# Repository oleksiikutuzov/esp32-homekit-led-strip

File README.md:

# esp32-homekit-led-strip
Native Apple HomeKit via an ESP32 for the NeoPixel LED Strip or any 5V LED Strip

Software is based on [HomeSpan](https://github.com/HomeSpan/HomeSpan) library. Supports RGB or RGBW Neopixel strips and optionally can act like a switch for any 5V electronics (Switch accessory in HomeKit can be shown as a Bulb, Socket or Fan).

_As usual, don't expect any warranties. I am just a hobbyist, not a professional. It works for me, but you take your own risk using it. I am not liable for any damage to your devices._

## Hardware

Custom PCB is designed for the project. Currently for regular ESP32 board, however there are plans to do for ESP32-C3, which has smaller footprint.

## HomeKit functions

Device has three modes, which can be switched via the Eve app. As they are custim characteristics, they are not visible in the Home app:
* Manual Control (manually set one single color)
* Rainbow (the whole strip is changing colors)
* Color Wheel (strip has different colors "running" along)

Also in the Eve app you can set the number of LEDs in your strip (default is 90). After changing this characteristic, you need to restart the controller for changes to take effect. 

Characteristics values are saved to NVS, so they will be restored if device looses power. 

At the moment you can enable the Switch device in the sketch by defining the `RELAY` variable, but in the future this will implemented via custom characteristic as well to be able to enable it when device is running.

## Software

Here you can see, which pins are used and pre-defined in the firmware:
```c++
 *                ESP-WROOM-32 Utilized pins
 *              ╔═════════════════════════════╗
 *              ║┌─┬─┐  ┌──┐  ┌─┐             ║
 *              ║│ | └──┘  └──┘ |             ║
 *              ║│ |            |             ║
 *              ╠═════════════════════════════╣
 *          +++ ║GND                       GND║ +++
 *          +++ ║3.3V                     IO23║ USED_FOR_NOTHING
 *              ║                         IO22║
 *              ║IO36                      IO1║ TX
 *              ║IO39                      IO3║ RX
 *              ║IO34                     IO21║
 *              ║IO35                         ║ NC
 *      RED_LED ║IO32                     IO19║
 *              ║IO33                     IO18║ RELAY
 *              ║IO25                      IO5║
 *              ║IO26                     IO17║ NEOPIXEL
 *              ║IO27                     IO16║
 *              ║IO14                      IO4║
 *              ║IO12                      IO0║ +++, BUTTON
 *              ╚═════════════════════════════╝
```

The firmware can be built and flashed using the Arduino IDE.

For this, you will need to add ESP32 support to it.

Furthermore, you will also need to install the following libraries using the Library Manager:

* HomeSpan

And some libraries manually:

1. Go to this GitHub repo and download it as a ZIP - [AsyncElegantOTA](https://github.com/ayushsharma82/AsyncElegantOTA)
2. In Arduino IDE select "Sketch" -> "Include Library" and "Add .ZIP Library..." and select downloaded ZIP
3. Do previous steps to the following libraries: 
   * [ESPAsyncWebServer](https://github.com/me-no-dev/ESPAsyncWebServer)
   * [AsyncTCP](https://github.com/me-no-dev/AsyncTCP)
4. Download and open this repository in Arduino IDE (or VSCode with Arduino extension)
5. Set the upload speed to 115200
6. Build, flash, and you're done

Instead of Arduino IDE OTA, the webserver update was implemented. You can flash binary at `http://[DEVICE IP]/update`.
There is a reboot link. Opening `http://[DEVICE IP]/reboot` will force the device to reboot. 

The device can also be controlled by the FLASH button on the board. More on [HomeSpan docs](https://github.com/HomeSpan/HomeSpan/blob/master/docs/UserGuide.md)

## Connect to HomeKit

1. Plug your LED Controller to power.
2. Press the FLASH button until the LED starts blinking rapidly and release it. Now it is in the configuration mode (More on [HomeSpan docs](https://github.com/HomeSpan/HomeSpan/blob/master/docs/UserGuide.md)). Press it two more times until the LED starts blinking 3 times in a row. This means mode 3 is chosen. Hold the button for 3-4 seconds once again and the WiFi AP will be started.
3. Go to WiFi settings on your iPhone/iPad and connect to the "HomeSpan-Setup" WiFi network.
4. You will choose your WiFi network and set the setup code for the accessory. 
5. Go to your Home app and select "Add Accessory"
6. Select "More Options" and you should see your LED Controller there.

## References and sources

- @HomeSpan for ESP32 HomeKit firmware [GitHub link](https://github.com/HomeSpan/HomeSpan)

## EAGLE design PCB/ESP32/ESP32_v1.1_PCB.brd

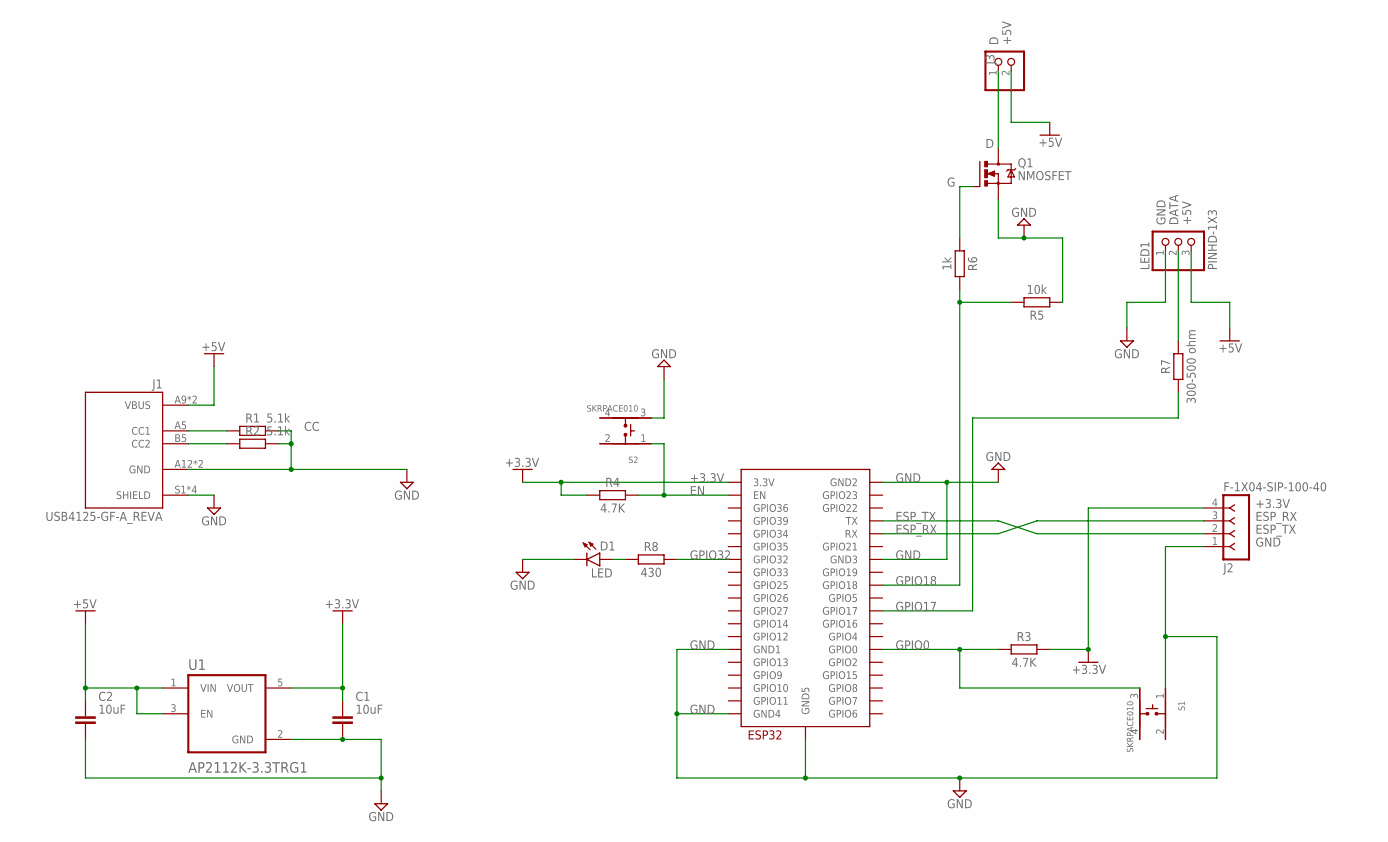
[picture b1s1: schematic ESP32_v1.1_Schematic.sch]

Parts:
C1, C2: 10uF; CAPC1608X85
D1: LED; LEDC1608X80N_FLAT-R
J1: USB4125-GF-A_REVA; GCT_USB4125-GF-A_REVA
J2: F-1X04-SIP-100-40; SIP-100-04-40
J3: PINHD-1X2; 1X02
LED1: PINHD-1X3; 1X03
Q1: NMOSFET; SOT23
R1, R2: 5.1k; RESC1608X60
R3, R4: 4.7K; RESC1608X60
R5: 10k; RESC1608X60
R6: 1k; RESC1608X60
R7: 300-500 ohm; RESC1608X60
R8: 430; RESC1608X60
S1, S2: SKRPACE010; SW_SKRPACE010
U1: AP2112K-3.3TRG1; SOT95P285X140-5N
U2: ESP32-WROOM

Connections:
+3.3V: C1.1, J2.4, R3.2, R4.1, U1.5 (VOUT), U2.3V3 (3.3V)
+5V: C2.1, J1.A9 (VBUS), J1.B9 (VBUS), J3.2, LED1.3, U1.1 (VIN), U1.3 (EN)
CC: J1.A5 (CC1), R1.1
D: J3.1, Q1.3 (D)
DATA: LED1.2, R7.2
EN: R4.2, S2.1, U2.EN
ESP_RX: J2.3, U2.RX
ESP_TX: J2.2, U2.TX
G: Q1.1 (G), R6.1
GND: C1.2, C2.2, D1.C, J1.A12 (GND), J1.B12 (GND), J1.S1 (SHIELD), J1.S2 (SHIELD), J1.S3 (SHIELD), J1.S4 (SHIELD), J2.1, LED1.1, Q1.2 (S), R1.2, R2.2, R5.1, S1.1, S2.3, U1.2 (GND), U2.GND1, U2.GND2, U2.GND3, U2.GND4, U2.GND5
GPIO0: R3.1, S1.3, U2.IO0 (GPIO0)
GPIO17: R7.1, U2.IO17 (GPIO17)
GPIO18: R5.2, R6.2, U2.IO18 (GPIO18)
GPIO32: R8.2, U2.IO32 (GPIO32)
LED: D1.A, R8.1
unnamed: J1.B5 (CC2), R2.1

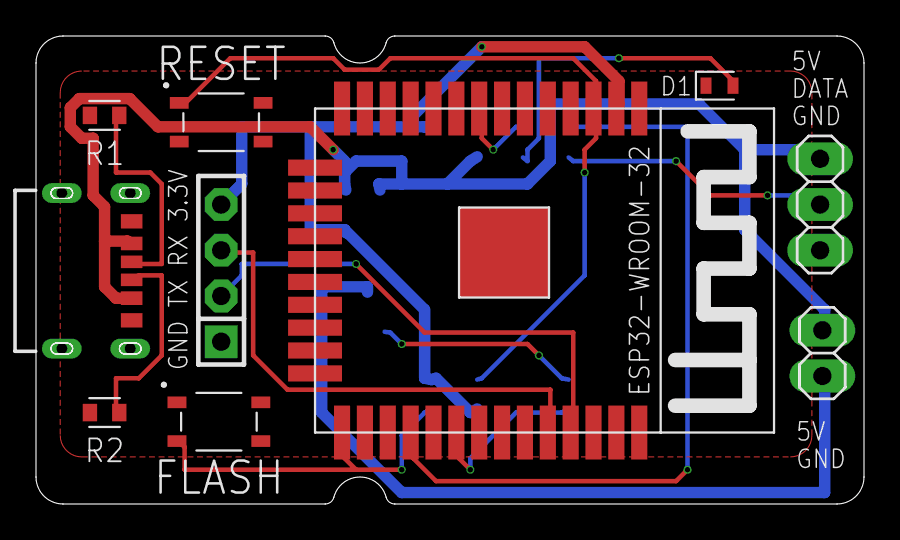
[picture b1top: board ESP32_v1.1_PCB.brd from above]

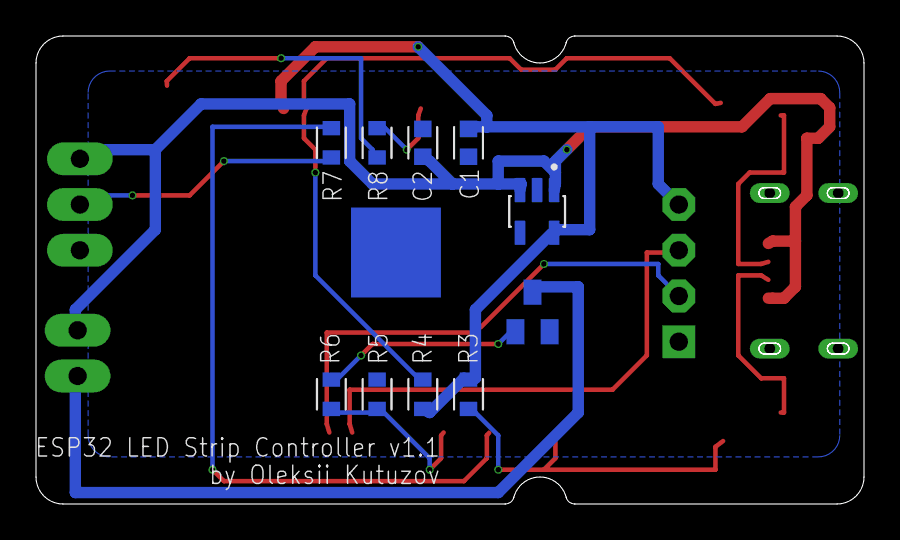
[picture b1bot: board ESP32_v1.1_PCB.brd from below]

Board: 2 copper layers, 46.0 x 26.0 mm, 20 parts (10 on the bottom side), 16 nets.

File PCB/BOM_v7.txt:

Part Value             Device                   Package               Description                                                                               
C1   10uF              C_CHIP-0603(1608-METRIC) CAPC1608X85           Capacitor - Generic  (voltage converter)                                                                     
C2   10uF              C_CHIP-0603(1608-METRIC) CAPC1608X85           Capacitor - Generic  (voltage converter)                                                   
C3   10uF              C_CHIP-0603(1608-METRIC) CAPC1608X85           Capacitor - Generic                                                                       
C4   10uF              C_CHIP-0603(1608-METRIC) CAPC1608X85           Capacitor - Generic                                                                       
C5   10uF              C_CHIP-0603(1608-METRIC) CAPC1608X85           Capacitor - Generic                                                                       
D1   LED               CHIP-FLAT-R_0603-0.80MM  LEDC1608X80N_FLAT-R                                                                                             
J1   USB4125-GF-A_REVA USB4125-GF-A_REVA        GCT_USB4125-GF-A_REVA USB 2.0 Type C Receptacle, Horizontal, SMT, For Power charging  Check prices Warning     
J2   F-1X04-SIP-100-40 F-1X04-SIP-100-40        SIP-100-04-40         FEMALE HEADER                                                                             
J3   PINHD-1X2         PINHD-1X2                1X02                  PIN HEADER                                                                                
LED1 PINHD-1X3         PINHD-1X3                1X03                  PIN HEADER                                                                                
Q1   NMOSFET           NMOSFET_SOT23            SOT23                 N-Channel MOSFET - Generic                                                                
R1   5.1k              R_CHIP-0603(1608-METRIC) RESC1608X60           Resistor Fixed - Generic                                                                  
R2   5.1k              R_CHIP-0603(1608-METRIC) RESC1608X60           Resistor Fixed - Generic                                                                  
R3   4.7K              R_CHIP-0603(1608-METRIC) RESC1608X60           Resistor Fixed - Generic                                                                  
R4   4.7K              R_CHIP-0603(1608-METRIC) RESC1608X60           Resistor Fixed - Generic                                                                  
R5   10k               R_CHIP-0603(1608-METRIC) RESC1608X60           Resistor Fixed - Generic                                                                  
R6   1k                R_CHIP-0603(1608-METRIC) RESC1608X60           Resistor Fixed - Generic                                                                  
R7   300-500 ohm       R_CHIP-0603(1608-METRIC) RESC1608X60           Resistor Fixed - Generic                                                                  
R8   430               R_CHIP-0603(1608-METRIC) RESC1608X60           Resistor Fixed - Generic                                                                  
S1   SKRPACE010        SKRPACE010               SW_SKRPACE010         Switch Tactile N.O. SPST Button J-Bend 0.05A 16VDC 2.55N SMD Automotive T/R              
S2   SKRPACE010        SKRPACE010               SW_SKRPACE010         Switch Tactile N.O. SPST Button J-Bend 0.05A 16VDC 2.55N SMD Automotive T/R                                                                                                                                                                                                             Maniufacturer Recommendations                                                                    
U1   AP2112K-3.3TRG1   AP2112K-3.3TRG1          SOT95P285X140-5N      AP2112 Series 0.6 A 3.3 V Fixed Output SMT LDO Linear Regulator - SOT23-5                
U2   ESP32-WROOM       ESP32-WROOM              ESP32-WROOM

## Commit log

2022-04-26 Add .clang-format, .gitignore
2022-04-26 Add .vscode folde
2022-04-26 Add basic led strip code
2022-04-26 Add OTA
2022-05-04 Add rainbow animations
2022-05-06 Add build action
2022-05-06 Edit build action script
2022-05-06 Add checkout for custom libraries
2022-05-06 Add sketch name
2022-05-06 Edit sketch name
2022-05-06 Move sketch to root
2022-05-06 Edit sketch names
2022-05-06 Put sketch back to folder
2022-05-06 Change platform url
2022-05-06 Add AsyncTCP custom library
2022-05-06 Add build parameters
2022-05-07 Add pins diagram, cleanup
2022-05-07 Reserve 5 socket connections and add comments
2022-05-08 Implement solid rainbow in HSV with variable V
2022-05-17 Redo rainbow wheel animation, schematic adjustment
2022-05-17 Add hardware files
2022-05-17 Update VSCode config
2022-05-17 Add Switch accessory for relay
2022-05-24 Cleanup, enable/disable relay in code
2022-05-26 Add custom characteristic of setting LEDs number in eve app
2022-05-30 Update settings file
2022-05-30 Prepare to dynamic add device function in HomeSpan
2022-05-30 Add render image
2022-05-30 Upload ESP32-C3 hardware files
2022-05-31 Organize Hardware files
2022-07-12 Add exporting prometheus metrics
2022-07-12 Add dynamic enabling of the switch accessory
2022-07-14 Saving switch status to NVS
2022-07-14 Show mac address as serial number
2022-08-09 Switch from ESPAsyncWebServer to WebServer
2022-08-17 Fix to animation, required HomeSpan version bump
2022-09-02 Implement OTA updates
2022-09-02 Quick fix
2022-09-02 Test update
2022-09-03 Read switch status from characteristic
2022-09-03 Increase update check interval to 1 hour
2022-09-05 Switch to PlatformIO
2022-09-05 test
2022-09-05 main
2022-09-06 Update (#13)
    * Switch to PlatformIO
2022-09-06 Add Auto Update Characteristic
2022-09-06 Show IP Address as Characteristic
2022-09-06 Add IP address and OTA Update switch Characteristics (#15)
    * Add Auto Update Characteristic
    * Show IP Address as Characteristic
2022-09-06 Remove file
2022-09-06 Fix update loop logic
2022-09-06 Update loop logic
2023-08-03 Update everything

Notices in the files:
parts and their libraries:
con-headers-jp: Copyright (C) 2008, Bob Starr
